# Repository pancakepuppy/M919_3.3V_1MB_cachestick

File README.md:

# M919_3.3V_1MB_cachestick
A 3.3V 1MB cache stick design for PCChips M919

(This design is only to be used with 3.3V processors. 5V/4V CPUs will violate the Absolute Maximum Terminal Voltage Relative to GND of the 3.3V SRAM chips which will likely result in permanent damage of the cache ICs.)

Design uses center power 0.400" 32-SOJ 128Kx8 3.3V SRAMs, which are available in speed grades of 8(less common)/10/12/15ns from several vendors. 
These parts should all fit this criteria:

71V124SA10/12/15Y

CY7C1019DV33-10VXI

CY7C1019BV33-10/12/15V

CY7C1019CV33-10/12/15V

IS63LV1024-8/10/12K

AS7C31025B-10/12/15J

AS7C31025C-10J

Bill of materials only has 3 different parts on it:

  Qty 18 - 0603 0.1uF 6.3V+ ceramic capacitors
  
  Qty 9 - SRAM parts as described above
  
  Qty 4 - 0603 33ohm convex 4resistor array
  
If you're experienced at hand soldering, the module is buildable this way (that's how I've built mine so far!)

I've been testing the module design with a 5x86-P75 (133MHz) at fastest L2 and DRAM settings and it has been very stable, running a number of DOS and Win95 benchmarks and tests (such as Quake, Doom, cachechk, Winstone 96, CPUmark99, Super PI) with no issues. 

If you want to have boards made with JLCPCB, upload the "UPLOAD_THIS_ZIP.zip" file in the /plotted_JLCsettings/ directory. It has the gerbers and drill files with their recommended plotting settings. Otherwise, plot however your board house recommends!

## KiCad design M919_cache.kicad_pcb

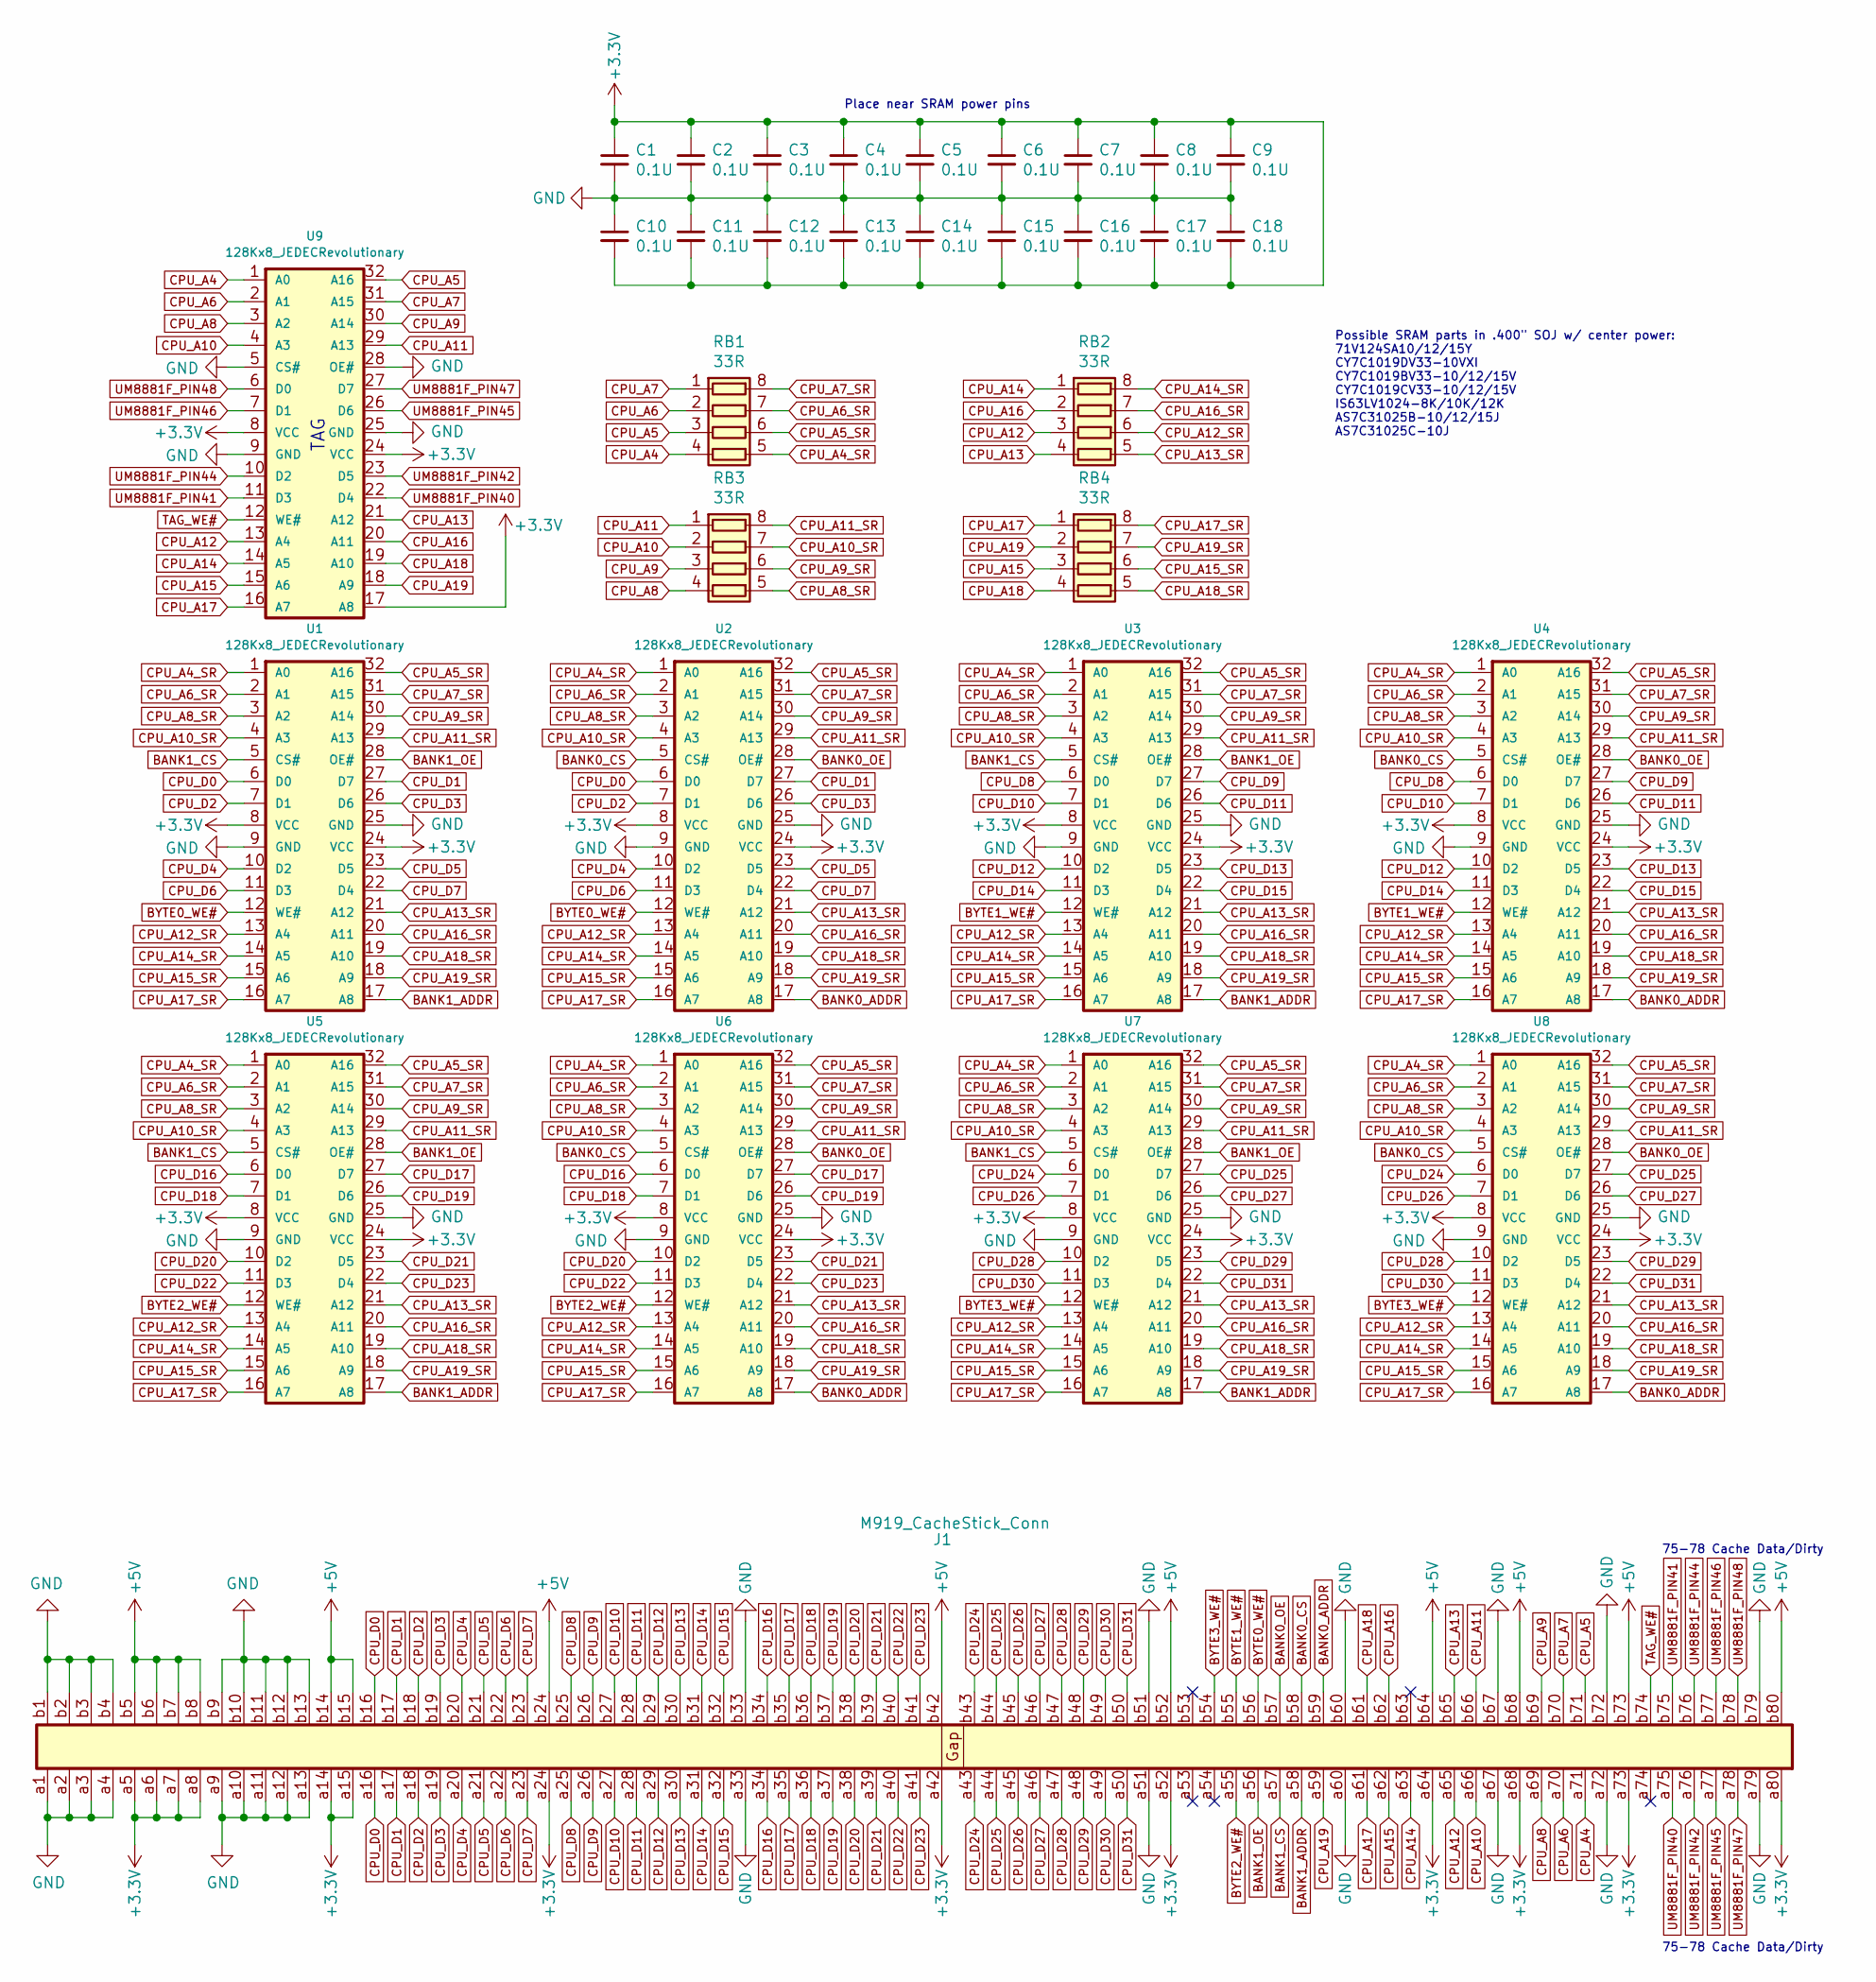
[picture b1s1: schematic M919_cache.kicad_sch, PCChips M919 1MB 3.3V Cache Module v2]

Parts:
C1, C2, C3, C4, C5, C6, C7, C8, C9, C10, C11, C12, C13, C14, C15, C16, C17, C18: 0.1U; C_0603_1608Metric
J1: M919_CacheStick_Conn; M919_cache_edgeconn
RB1, RB2, RB3, RB4: 33R; R_Array_Convex_4x0603
U1, U2, U3, U4, U5, U6, U7, U8, U9: 128Kx8_JEDECRevolutionary; 32-SOJ_400mil

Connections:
+3V3: C1.1, C2.1, C3.1, C4.1, C5.1, C6.1, C7.1, C8.1, C9.1, C10.2, C11.2, C12.2, C13.2, C14.2, C15.2, C16.2, C17.2, C18.2, J1.a5, J1.a6, J1.a7, J1.a8, J1.a14, J1.a15, J1.a24, J1.a42, J1.a52, J1.a64, J1.a68, J1.a73, J1.a80, U1.8 (VCC), U1.24 (VCC), U2.8 (VCC), U2.24 (VCC), U3.8 (VCC), U3.24 (VCC), U4.8 (VCC), U4.24 (VCC), U5.8 (VCC), U5.24 (VCC), U6.8 (VCC), U6.24 (VCC), U7.8 (VCC), U7.24 (VCC), U8.8 (VCC), U8.24 (VCC), U9.8 (VCC), U9.17 (A8), U9.24 (VCC)
+5V: J1.b5, J1.b6, J1.b7, J1.b8, J1.b14, J1.b15, J1.b24, J1.b42, J1.b52, J1.b64, J1.b68, J1.b73, J1.b80
BANK0_ADDR: J1.b59, U2.17 (A8), U4.17 (A8), U6.17 (A8), U8.17 (A8)
BANK0_CS: J1.b58, U2.5 (CS#), U4.5 (CS#), U6.5 (CS#), U8.5 (CS#)
BANK0_OE: J1.b57, U2.28 (OE#), U4.28 (OE#), U6.28 (OE#), U8.28 (OE#)
BANK1_ADDR: J1.a58, U1.17 (A8), U3.17 (A8), U5.17 (A8), U7.17 (A8)
BANK1_CS: J1.a57, U1.5 (CS#), U3.5 (CS#), U5.5 (CS#), U7.5 (CS#)
BANK1_OE: J1.a56, U1.28 (OE#), U3.28 (OE#), U5.28 (OE#), U7.28 (OE#)
BYTE0_WE#: J1.b56, U1.12 (WE#), U2.12 (WE#)
BYTE1_WE#: J1.b55, U3.12 (WE#), U4.12 (WE#)
BYTE2_WE#: J1.a55, U5.12 (WE#), U6.12 (WE#)
BYTE3_WE#: J1.b54, U7.12 (WE#), U8.12 (WE#)
CPU_A4: J1.a71, RB1.4 (R4.1), U9.1 (A0)
CPU_A4_SR: RB1.5 (R4.2), U1.1 (A0), U2.1 (A0), U3.1 (A0), U4.1 (A0), U5.1 (A0), U6.1 (A0), U7.1 (A0), U8.1 (A0)
CPU_A5: J1.b71, RB1.3 (R3.1), U9.32 (A16)
CPU_A5_SR: RB1.6 (R3.2), U1.32 (A16), U2.32 (A16), U3.32 (A16), U4.32 (A16), U5.32 (A16), U6.32 (A16), U7.32 (A16), U8.32 (A16)
CPU_A6: J1.a70, RB1.2 (R2.1), U9.2 (A1)
CPU_A6_SR: RB1.7 (R2.2), U1.2 (A1), U2.2 (A1), U3.2 (A1), U4.2 (A1), U5.2 (A1), U6.2 (A1), U7.2 (A1), U8.2 (A1)
CPU_A7: J1.b70, RB1.1 (R1.1), U9.31 (A15)
CPU_A7_SR: RB1.8 (R1.2), U1.31 (A15), U2.31 (A15), U3.31 (A15), U4.31 (A15), U5.31 (A15), U6.31 (A15), U7.31 (A15), U8.31 (A15)
CPU_A8: J1.a69, RB3.4 (R4.1), U9.3 (A2)
CPU_A8_SR: RB3.5 (R4.2), U1.3 (A2), U2.3 (A2), U3.3 (A2), U4.3 (A2), U5.3 (A2), U6.3 (A2), U7.3 (A2), U8.3 (A2)
CPU_A9: J1.b69, RB3.3 (R3.1), U9.30 (A14)
CPU_A9_SR: RB3.6 (R3.2), U1.30 (A14), U2.30 (A14), U3.30 (A14), U4.30 (A14), U5.30 (A14), U6.30 (A14), U7.30 (A14), U8.30 (A14)
CPU_A10: J1.a66, RB3.2 (R2.1), U9.4 (A3)
CPU_A10_SR: RB3.7 (R2.2), U1.4 (A3), U2.4 (A3), U3.4 (A3), U4.4 (A3), U5.4 (A3), U6.4 (A3), U7.4 (A3), U8.4 (A3)
CPU_A11: J1.b66, RB3.1 (R1.1), U9.29 (A13)
CPU_A11_SR: RB3.8 (R1.2), U1.29 (A13), U2.29 (A13), U3.29 (A13), U4.29 (A13), U5.29 (A13), U6.29 (A13), U7.29 (A13), U8.29 (A13)
CPU_A12: J1.a65, RB2.3 (R3.1), U9.13 (A4)
CPU_A12_SR: RB2.6 (R3.2), U1.13 (A4), U2.13 (A4), U3.13 (A4), U4.13 (A4), U5.13 (A4), U6.13 (A4), U7.13 (A4), U8.13 (A4)
CPU_A13: J1.b65, RB2.4 (R4.1), U9.21 (A12)
CPU_A13_SR: RB2.5 (R4.2), U1.21 (A12), U2.21 (A12), U3.21 (A12), U4.21 (A12), U5.21 (A12), U6.21 (A12), U7.21 (A12), U8.21 (A12)
CPU_A14: J1.a63, RB2.1 (R1.1), U9.14 (A5)
CPU_A14_SR: RB2.8 (R1.2), U1.14 (A5), U2.14 (A5), U3.14 (A5), U4.14 (A5), U5.14 (A5), U6.14 (A5), U7.14 (A5), U8.14 (A5)
CPU_A15: J1.a62, RB4.3 (R3.1), U9.15 (A6)
CPU_A15_SR: RB4.6 (R3.2), U1.15 (A6), U2.15 (A6), U3.15 (A6), U4.15 (A6), U5.15 (A6), U6.15 (A6), U7.15 (A6), U8.15 (A6)
CPU_A16: J1.b62, RB2.2 (R2.1), U9.20 (A11)
CPU_A16_SR: RB2.7 (R2.2), U1.20 (A11), U2.20 (A11), U3.20 (A11), U4.20 (A11), U5.20 (A11), U6.20 (A11), U7.20 (A11), U8.20 (A11)
CPU_A17: J1.a61, RB4.1 (R1.1), U9.16 (A7)
CPU_A17_SR: RB4.8 (R1.2), U1.16 (A7), U2.16 (A7), U3.16 (A7), U4.16 (A7), U5.16 (A7), U6.16 (A7), U7.16 (A7), U8.16 (A7)
CPU_A18: J1.b61, RB4.4 (R4.1), U9.19 (A10)
CPU_A18_SR: RB4.5 (R4.2), U1.19 (A10), U2.19 (A10), U3.19 (A10), U4.19 (A10), U5.19 (A10), U6.19 (A10), U7.19 (A10), U8.19 (A10)
CPU_A19: J1.a59, RB4.2 (R2.1), U9.18 (A9)
CPU_A19_SR: RB4.7 (R2.2), U1.18 (A9), U2.18 (A9), U3.18 (A9), U4.18 (A9), U5.18 (A9), U6.18 (A9), U7.18 (A9), U8.18 (A9)
CPU_D0: J1.a16, J1.b16, U1.6 (D0), U2.6 (D0)
CPU_D1: J1.a17, J1.b17, U1.27 (D7), U2.27 (D7)
CPU_D2: J1.a18, J1.b18, U1.7 (D1), U2.7 (D1)
CPU_D3: J1.a19, J1.b19, U1.26 (D6), U2.26 (D6)
CPU_D4: J1.a20, J1.b20, U1.10 (D2), U2.10 (D2)
CPU_D5: J1.a21, J1.b21, U1.23 (D5), U2.23 (D5)
CPU_D6: J1.a22, J1.b22, U1.11 (D3), U2.11 (D3)
CPU_D7: J1.a23, J1.b23, U1.22 (D4), U2.22 (D4)
CPU_D8: J1.a25, J1.b25, U3.6 (D0), U4.6 (D0)
CPU_D9: J1.a26, J1.b26, U3.27 (D7), U4.27 (D7)
CPU_D10: J1.a27, J1.b27, U3.7 (D1), U4.7 (D1)
CPU_D11: J1.a28, J1.b28, U3.26 (D6), U4.26 (D6)
CPU_D12: J1.a29, J1.b29, U3.10 (D2), U4.10 (D2)
CPU_D13: J1.a30, J1.b30, U3.23 (D5), U4.23 (D5)
CPU_D14: J1.a31, J1.b31, U3.11 (D3), U4.11 (D3)
CPU_D15: J1.a32, J1.b32, U3.22 (D4), U4.22 (D4)
CPU_D16: J1.a34, J1.b34, U5.6 (D0), U6.6 (D0)
CPU_D17: J1.a35, J1.b35, U5.27 (D7), U6.27 (D7)
CPU_D18: J1.a36, J1.b36, U5.7 (D1), U6.7 (D1)
CPU_D19: J1.a37, J1.b37, U5.26 (D6), U6.26 (D6)
CPU_D20: J1.a38, J1.b38, U5.10 (D2), U6.10 (D2)
CPU_D21: J1.a39, J1.b39, U5.23 (D5), U6.23 (D5)
CPU_D22: J1.a40, J1.b40, U5.11 (D3), U6.11 (D3)
CPU_D23: J1.a41, J1.b41, U5.22 (D4), U6.22 (D4)
CPU_D24: J1.a43, J1.b43, U7.6 (D0), U8.6 (D0)
CPU_D25: J1.a44, J1.b44, U7.27 (D7), U8.27 (D7)
CPU_D26: J1.a45, J1.b45, U7.7 (D1), U8.7 (D1)
CPU_D27: J1.a46, J1.b46, U7.26 (D6), U8.26 (D6)
CPU_D28: J1.a47, J1.b47, U7.10 (D2), U8.10 (D2)
CPU_D29: J1.a48, J1.b48, U7.23 (D5), U8.23 (D5)
CPU_D30: J1.a49, J1.b49, U7.11 (D3), U8.11 (D3)
CPU_D31: J1.a50, J1.b50, U7.22 (D4), U8.22 (D4)
GND: C1.2, C2.2, C3.2, C4.2, C5.2, C6.2, C7.2, C8.2, C9.2, C10.1, C11.1, C12.1, C13.1, C14.1, C15.1, C16.1, C17.1, C18.1, J1.a1, J1.a2, J1.a3, J1.a4, J1.a9, J1.a10, J1.a11, J1.a12, J1.a13, J1.a33, J1.a51, J1.a60, J1.a67, J1.a72, J1.a79, J1.b1, J1.b2, J1.b3, J1.b4, J1.b9, J1.b10, J1.b11, J1.b12, J1.b13, J1.b33, J1.b51, J1.b60, J1.b67, J1.b72, J1.b79, U1.9 (GND), U1.25 (GND), U2.9 (GND), U2.25 (GND), U3.9 (GND), U3.25 (GND), U4.9 (GND), U4.25 (GND), U5.9 (GND), U5.25 (GND), U6.9 (GND), U6.25 (GND), U7.9 (GND), U7.25 (GND), U8.9 (GND), U8.25 (GND), U9.5 (CS#), U9.9 (GND), U9.25 (GND), U9.28 (OE#)
TAG_WE#: J1.b74, U9.12 (WE#)
UM8881F_PIN40: J1.a75, U9.22 (D4)
UM8881F_PIN41: J1.b75, U9.11 (D3)
UM8881F_PIN42: J1.a76, U9.23 (D5)
UM8881F_PIN44: J1.b76, U9.10 (D2)
UM8881F_PIN45: J1.a77, U9.26 (D6)
UM8881F_PIN46: J1.b77, U9.7 (D1)
UM8881F_PIN47: J1.a78, U9.27 (D7)
UM8881F_PIN48: J1.b78, U9.6 (D0)

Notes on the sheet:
75-78 Cache Data/Dirty
Possible SRAM parts in .400" SOJ w/ center power: 71V124SA10/12/15Y CY7C1019DV33-10VXI CY7C1019BV33-10/12/15V CY7C1019CV33-10/12/15V IS63LV1024-8K/10K/12K AS7C31025B-10/12/15J AS7C31025C-10J
Place near SRAM power pins
TAG

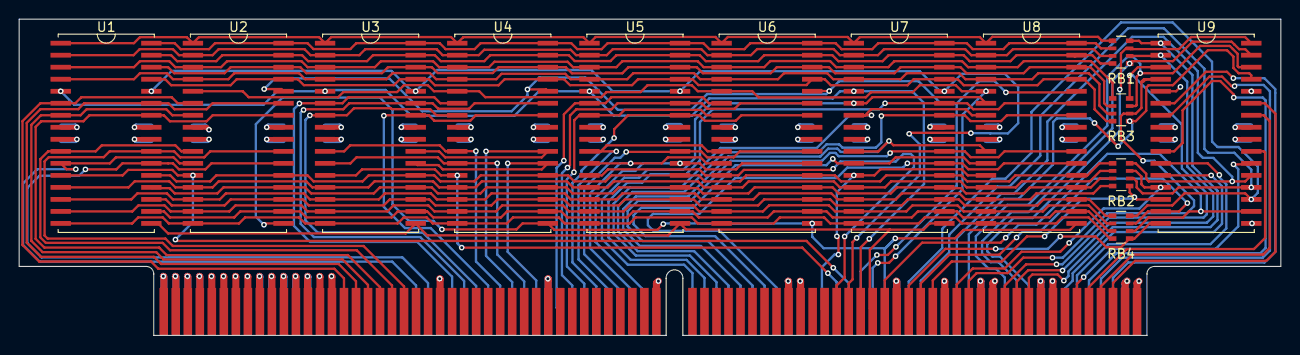
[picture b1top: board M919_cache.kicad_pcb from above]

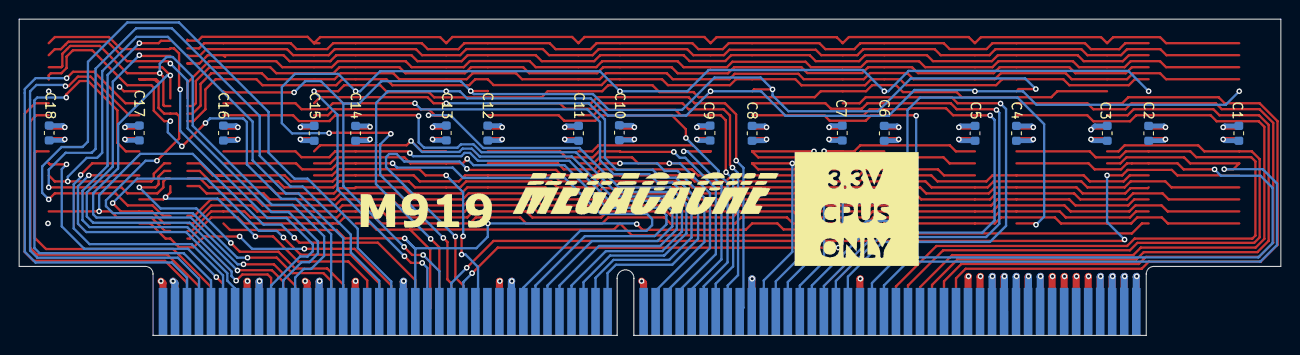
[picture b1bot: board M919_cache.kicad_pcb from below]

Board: 4 copper layers, 133.4 x 33.4 mm, 32 parts (18 on the bottom side), 86 nets.

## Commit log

2022-01-27 Updated PDF schematics
